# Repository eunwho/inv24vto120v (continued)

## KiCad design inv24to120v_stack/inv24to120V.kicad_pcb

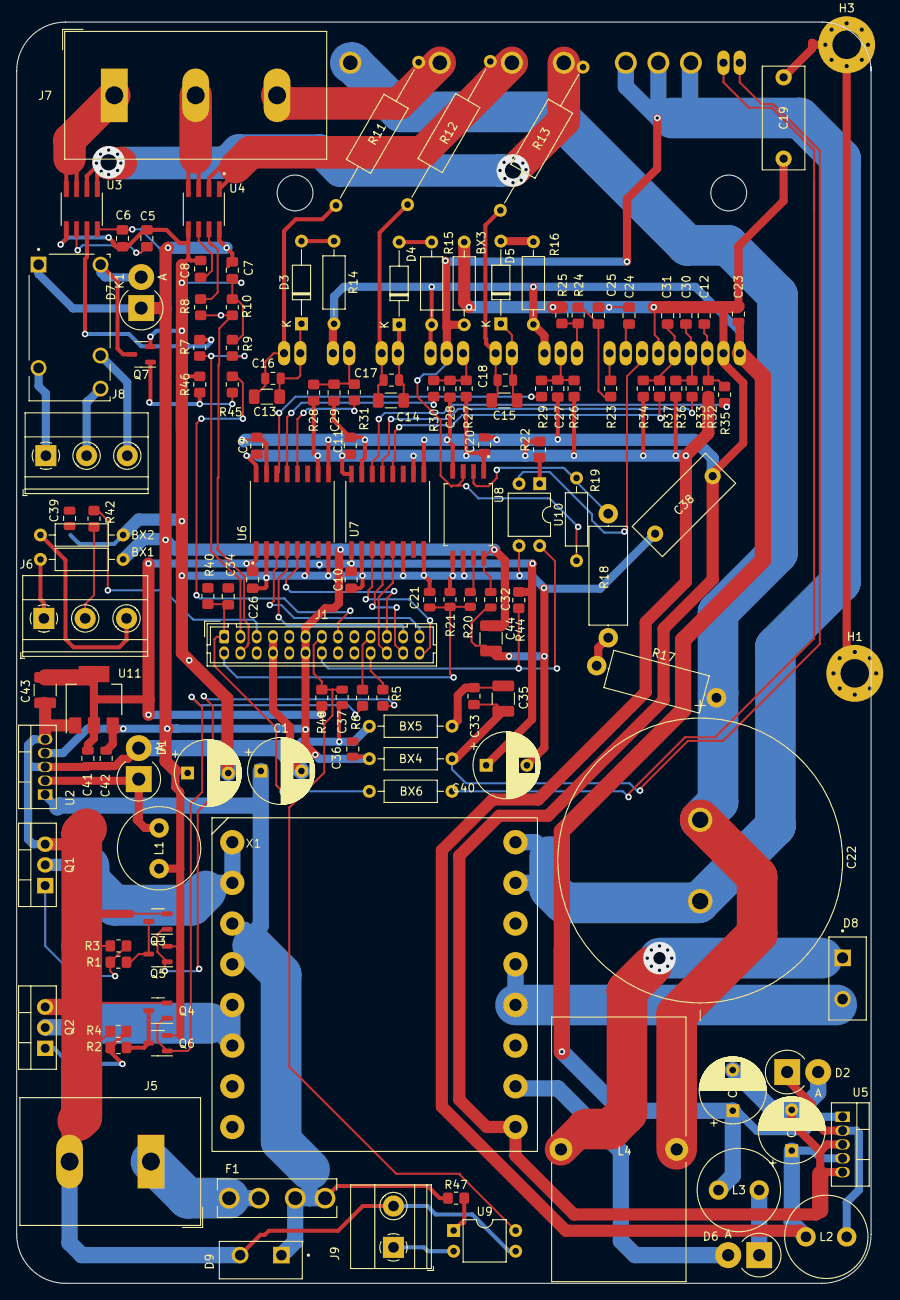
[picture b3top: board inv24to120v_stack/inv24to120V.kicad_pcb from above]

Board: 2 copper layers, 105.0 x 155.0 mm, 136 parts (1 on the bottom side), 93 nets.

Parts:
BX1, BX2, BX3, BX4, BX5, BX6: 0; R_Axial_DIN0207_L6.3mm_D2.5mm_P10.16mm_Horizontal
C1, C2, C4, C40: 100uF/50V; CP_Radial_D8.0mm_P5.00mm
C3: 470uF/50V; CP_Radial_D8.0mm_P5.00mm
C5, C8, C12, C25, C27, C28, C29, C30, C31: 102; C_0805_2012Metric_Pad1.18x1.45mm_HandSolder
C6, C7, C9, C10, C11, C26, C33, C34: 104; C_0805_2012Metric_Pad1.18x1.45mm_HandSolder
C13, C14, C15: 22uF/25V; C_1206_3216Metric_Pad1.33x1.80mm_HandSolder
C16, C17, C18, C20, C21, C23, C32, C36, C37, C39, C41, C42: 104; C_0805_2012Metric
C19, C38: 102; C_Disc_D12.5mm_W5.0mm_P10.00mm
C22: 470uF/400V; CAPPRD1000W160D3600H5200
C24: 333; C_0805_2012Metric_Pad1.18x1.45mm_HandSolder
C35, C43, C44: 22uF/10V; C_1210_3225Metric_Pad1.33x2.70mm_HandSolder
D1, D2, D6: 1N5822; D_DO-201AD_P3.81mm_Vertical_AnodeUp
D3, D4, D5: 1N4937; D_DO-35_SOD27_P10.16mm_Horizontal
D7: 1N4002; D_DO-201AD_P3.81mm_Vertical_AnodeUp
D8, D9: BYV29X-500; TO507P1020X460X2000-2
F1: 3544-2; FUSE_3544-2
H1, H3: MountingHole_Pad; MountingHole_3.5mm_Pad_Via
IC1: FSAM50SM60A; DIP-32
J1: Conn_02x13_Odd_Even; Hirose_DF11-26DP-2DSA_2x13_P2.00mm_Vertical
J5: Screw_Terminal_01x02; TerminalBlock_Dinkle_DT-55-B01X-02_P10.00mm
J6: Screw_Terminal_01x03; TerminalBlock_Phoenix_MKDS-1,5-3-5.08_1x03_P5.08mm_Horizont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
J7: Screw_Terminal_01x03; TerminalBlock_Dinkle_DT-55-B01X-03_P10.00mm
J8: Screw_Terminal_01x03; TerminalBlock_Phoenix_MKDS-1,5-3_1x03_P5.00mm_Horizontal
J9: Screw_Terminal_01x02; TerminalBlock_Phoenix_MKDS-1,5-2-5.08_1x02_P5.08mm_Horizont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
K1: J0971CS5VDC.45; RELAY_J0971CS5VDC.45
L1, L2, L3: 100uH; L_Radial_D10.0mm_P5.00mm_Neosid_SD12k_style3
L4: 22uH; IND_HCTI-10-20.0
Q1, Q2: IRFZ44NPBF; TO-220-3_Vertical
Q3, Q4: 2SC1815_SOT32; SOT-23-3
Q5, Q6: 2SA1015_SOT32; SOT-23-3
Q7: 2SC1815; SOT-23-3
R1, R2: 10; R_0805_2012Metric_Pad1.20x1.40mm_HandSolder
R3, R4, R40: 10K; R_0805_2012Metric_Pad1.20x1.40mm_HandSolder
R5, R6, R29, R30, R31, R32, R33, R34: 100; R_0805_2012Metric_Pad1.20x1.40mm_HandSolder
R7, R8, R9, R10: 2K; R_0805_2012Metric_Pad1.20x1.40mm_HandSolder
R11, R12, R13: 5.6; R_Axial_DIN0309_L9.0mm_D3.2mm_P20.32mm_Horizontal
R14, R15, R16: 20; R_Axial_DIN0207_L6.3mm_D2.5mm_P10.16mm_Horizontal
R17, R18: 1M/2W; R_Axial_DIN0414_L11.9mm_D4.5mm_P15.24mm_Horizontal
R19: 1K; R_Axial_DIN0207_L6.3mm_D2.5mm_P10.16mm_Horizontal
R20, R21: 2K; R_0805_2012Metric
R22, R45: 470; R_0805_2012Metric_Pad1.20x1.40mm_HandSolder
R23: 390; R_0805_2012Metric_Pad1.20x1.40mm_HandSolder
R24: 3.9K; R_0805_2012Metric_Pad1.20x1.40mm_HandSolder
R25: 45; R_0805_2012Metric_Pad1.20x1.40mm_HandSolder
R26, R27, R28, R35, R36, R37, R42, R44, R46, R48: 4.7K; R_0805_2012Metric_Pad1.20x1.40mm_HandSolder
R47: 2k; R_0805_2012Metric_Pad1.20x1.40mm_HandSolder
U2, U5: LM2576HVT-5; TO-220-5_Vertical
U3, U4: ACS712ELCTR30AT; SOIC127P600X175-8N
U6, U7: ISO7340CDW; SOIC127P1030X265-16N
U8: AMC1300BDWVR; SOIC127P1150X280-8N
U9, U10: PC817; DIP-4_W7.62mm
U11: LM1117MP-3.3; SOT-223-3_TabPin2
X1: ee42208x8p

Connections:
150V_OUT: D8.2 (A), X1.12, X1.13
+3.3V: C10.1, C26.1, C40.1, C41.2, C43.1, R44.1, R48.2, U6.1 (VCC1), U7.1 (VCC1), U11.2 (VO)
+5V: BX1.2, BX4.1, C2.1, C6.2, C7.2, C32.2, C36.2, C42.2, C44.1, D7.1 (K), J1.11, J1.12, K1.A1, L1.2, Q5.2 (E), Q6.2 (E), U2.4 (FB), U3.8 (VCC), U4.8 (VCC), U8.8 (VDD2), U11.3 (VI)
+5VP: C4.1, C9.1, C11.2, C20.1, L2.2, R22.2, R26.2, R27.2, R28.2, R35.2, R36.2, R37.2, U5.4 (FB), U6.10 (EN), U6.16 (VCC2), U7.10 (EN), U7.16 (VCC2), U8.1 (VDD1)
+15V: C3.1, C23.1, IC1.1 (VCC(L)), IC1.12 (VCC(UH)), IC1.17 (VCC(VH)), IC1.21 (VCC(WH)), L3.2, R14.2, R15.2, R16.2, U5.1 (VIN)
+24V: C1.1, D9.1 (K), F1.2_1, F1.2_2, R47.1, U2.1 (VIN), X1.3, X1.4
/W_phase: IC1.31 (W), J7.3, R11.1
/pri1: Q1.2 (D), X1.1, X1.2
/pri2: Q2.2 (D), X1.5, X1.6
ANALOG_CMD: C39.2, J1.5, R42.1
DIGITAL_CMD: C37.2, J1.13, R48.1, U9.4
Earth_Protective: C19.2, H1.1, H3.1
FAULT_IPM: J1.14, R44.2, U10.4
GND: BX2.2, BX5.1, C1.2, C2.2, C5.2, C6.1, C7.1, C8.2, C10.2, C21.1, C26.2, C32.1, C34.1, C36.1, C37.1, C38.1, C39.1, C40.2, C41.1, C42.1, C43.2, C44.2, D1.2 (A), D9.2 (A), J1.7, J1.8, J5.2, J9.2, Q1.3 (S), Q2.3 (S), Q3.2 (E), Q4.2 (E), Q7.2 (E), R3.1, R4.1, R9.1, R10.1, R21.1, R40.1, R46.2, U2.3 (GND), U2.5 (~ON/OFF), U3.5 (GND), U4.5 (GND), U6.2 (GND1), U6.6 (IND), U6.8 (GND1-1), U7.2 (GND1), U7.6 (IND), U7.8 (GND1-1), U8.5 (GND2), U8.6 (OUTN), U9.3, U10.3, U11.1 (GND)
GND2: BX3.1, C3.2, C4.2, C9.2, C11.1, C12.1, C19.1, C20.2, C23.2, C24.2, C25.2, C27.1, C28.1, C29.1, C30.1, C31.1, C38.2, D2.2 (A), IC1.2 (COM(L)), IC1.6 (COM(L)), R25.1, U5.3 (GND), U5.5 (~ON/OFF), U6.9 (GND2), U6.15 (GND2-1), U7.9 (GND2), U7.15 (GND2-1), U8.4 (GND1), X1.9
GNDPWR: BX3.2, C22.2, IC1.16 (COM(H)), IC1.26 (NU), IC1.27 (NV), IC1.28 (NW), R19.1, U8.3 (INN), X1.15, X1.16
H+15V: D6.2 (A), X1.10
IN_UH: C27.2, IC1.11 (IN_UH), R26.1, R29.2
IN_UL: C12.2, IC1.3 (IN_UL), R32.2, R35.1
IN_VH: C28.2, IC1.15 (IN_VH), R27.1, R30.2
IN_VL: C30.2, IC1.4 (IN_VL), R33.2, R36.1
IN_WH: C29.2, IC1.20 (IN_WH), R28.1, R31.2
IN_WL: C31.2, IC1.5 (IN_WL), R34.2, R37.1
I_Uphase: J1.3, R7.1, R9.2
I_Vphase: J1.4, R8.1, R10.2
unnamed: BX5.2, C33.1, C35.2
unnamed: C25.1, R23.1, R24.1
unnamed: D1.1 (K), L1.1, U2.2 (OUT)
unnamed: D2.1 (K), L2.1, U5.2 (OUT)
unnamed: D3.2 (A), R14.1
unnamed: C13.1, C16.1, D3.1 (K), IC1.22 (VB(W))
unnamed: D4.2 (A), R15.1
unnamed: C14.1, C17.1, D4.1 (K), IC1.18 (VB(V))
unnamed: D5.2 (A), R16.1
unnamed: C15.1, C18.1, D5.1 (K), IC1.13 (VB(U))
unnamed: D6.1 (K), L3.1
unnamed: D7.2 (A), K1.A2, Q7.3 (C)
unnamed: D8.1 (K), L4.2
unnamed: C24.1, IC1.8 (CFOD)
unnamed: IC1.9 (CSC), R23.2
unnamed: IC1.10 (RSC), R24.2, R25.2
unnamed: BX6.2, IC1.25 (RTH)
unnamed: IC1.7 (VFO), U10.2
unnamed: C15.2, C18.2, IC1.14 (VS(U)), R13.2
unnamed: C14.2, C17.2, IC1.19 (VS(V)), R12.2
unnamed: C13.2, C16.2, IC1.23 (VS(W)), R11.2
unnamed: F1.1_1, F1.1_2, J5.1
unnamed: BX1.1, J6.1
unnamed: J6.2, R42.2
unnamed: BX2.1, J6.3
unnamed: J8.1, K1.11
unnamed: J8.2, K1.14
unnamed: J8.3, K1.12
unnamed: J9.1, U9.2
unnamed: Q1.1 (G), R1.2, R3.2
unnamed: Q2.1 (G), R2.2, R4.2
unnamed: Q3.1 (B), Q5.1 (B), R5.2
unnamed: Q3.3 (C), Q5.3 (C), R1.1
unnamed: Q4.1 (B), Q6.1 (B), R6.2
unnamed: Q4.3 (C), Q6.3 (C), R2.1
unnamed: Q7.1 (B), R45.2, R46.1
unnamed: R17.1, R18.2
unnamed: R22.1, U10.1
unnamed: R47.2, U9.1
unnamed: C5.1, U3.6 (FILTER)
unnamed: R7.2, U3.7 (VIOUT)
unnamed: C8.1, U4.6 (FILTER)
unnamed: R8.2, U4.7 (VIOUT)
unnamed: R29.1, U6.14 (OUTA)
unnamed: R30.1, U6.13 (OUTB)
unnamed: R31.1, U6.12 (OUTC)
unnamed: R32.1, U7.14 (OUTA)
unnamed: R33.1, U7.13 (OUTB)
unnamed: R34.1, U7.12 (OUTC)
unnamed: R18.1, R19.2, U8.2 (INP)
unnamed: R20.2, U8.7 (OUTP)
PWM0_H: J1.25, U6.3 (INA)
PWM0_L: J1.26, U7.3 (INA)
PWM1_H: J1.23, U6.4 (INB)
PWM1_L: J1.24, U7.4 (INB)
PWM2_H: J1.21, U6.5 (INC)
PWM2_L: J1.22, U7.5 (INC)
PWM_A: J1.20, R5.1
PWM_B: J1.19, R6.1
RELAY_TRIP: J1.15, R45.1
TEMPERATURE_IPM: BX6.1, C34.2, J1.1, R40.2
U_phase: J7.1, U3.3 (IP-), U3.4 (IP-)
U_sensor: IC1.29 (U), R13.1, U3.1 (IP+), U3.2 (IP+)
VBUS: C22.1, IC1.32, L4.1, R17.2
VDC_sensor: C21.2, J1.2, R20.1, R21.2
VTH_IPM: BX4.2, C33.2, C35.1, IC1.24 (VTH)
V_phase: J7.2, U4.3 (IP-), U4.4 (IP-)
V_sensor: IC1.30 (V), R12.1, U4.1 (IP+), U4.2 (IP+)

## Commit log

2023-11-20 first add commit
2023-11-21 start rout
2023-11-23 add class name
2023-12-09 remove aux addon connect
2023-12-11 place parts
2023-12-27 route done
2023-12-27 edit reference
2023-12-29 rout finish
2024-04-15 for 220V fan control
2024-04-15 to pcb fix error
2024-04-21 start place parts
2024-04-28 fsam05 before change to NFA50460R4B
2024-04-28 before delete isolation
2024-04-29 non isolate inverter place parts,
2024-04-29 fix 35313-0460 0260 dip se 3d model
2024-07-01 change IPM to STGIF7CH60TS
2024-07-04 sch design 1st done
2024-07-05 start place component
2024-07-16 add pause cause mati argue
2024-07-17 finish routing next add copper for power
2024-07-17 renumber ref and schematic 적용
2024-07-19 check DRC
2024-07-23 plot gerber
